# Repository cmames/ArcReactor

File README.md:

# ⚛️ Arc Reactor Mark II - Open Source Prop Replica

## Project Overview
This project provides all necessary files (Electronics, 3D Models, and Firmware) to build a sophisticated, functional replica of the Mark II Arc Reactor with an emphasis on realistic plasma motion effects.

The design focuses on a premium, compact, and fully wireless solution for a dynamic display prop. The core feature is the smooth, chaotic rotation effect of the ice-blue plasma filaments, controlled by custom firmware.

## Key Features
* **Ice-Blue Plasma Effect:** Uses 5 custom LED filaments (300mm length) controlled via PWM for dynamic, realistic light effects (rotation, chaos, flickering).
* **Standalone Power:** Features an integrated Li-Po battery (150-200mAh) and a full power management system (TP4056 for charging, Mini Boost to 5V).
* **Amovibility & Latency:** Designed to be easily detached from its magnetic display stand, maintaining the light effect for a short duration thanks to the embedded power system.
* **Microcontroller:** ESP32-C3 Mini for high-speed PWM control (5 dedicated LEDC channels) and battery monitoring (ADC).
* **SMD Component Integration:** Custom circular PCB design utilizing SOT-23 MOSFETs for minimal footprint and optimal soldering simplicity.
* **Optics:** Use of a 3D-printed transparent PETG for superior light diffusion and visual quality.

## Project Files Included
This repository is organized into the following directories:

| Directory | Content | Description |
| :--- | :--- | :--- |
| **`Firmware/`** | Arduino/PlatformIO Code | Source code (C/C++) for the ESP32-C3, including PWM routines, ADC battery monitoring, and the 'flicker/fade-out' logic. |
| **`Electronics/`** | KiCad Project Files | Schematics, PCB layout files (circular design), and custom component libraries (e.g., SOT-23 footprints, ESP32-C3 module). |
| **`Mechanical/`** | STL / FreeCAD Files | 3D models for the reactor casing, the flexible TPU casting mold, and the magnetic display stand components. |
| **`Documentation/`** | Datasheets & Guides | Bill of Materials (BOM), wiring diagrams, and assembly guides. |

## License
This project is released under the **GNU General Public License v3.0 (GPL-3.0)**. See the `LICENSE` file for more details.

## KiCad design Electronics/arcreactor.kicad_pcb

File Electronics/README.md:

# ⚛️ Arc Reactor Mark II - Open Source Prop Replica

| Directory | Content | Description |
| :--- | :--- | :--- |
| **`Electronics/`** | KiCad Project Files | Schematics, PCB layout files (circular design), and custom component libraries (e.g., SOT-23 footprints, ESP32-C3 module). |

## License
This project is released under the **GNU General Public License v3.0 (GPL-3.0)**. See the `LICENSE` file for more details.

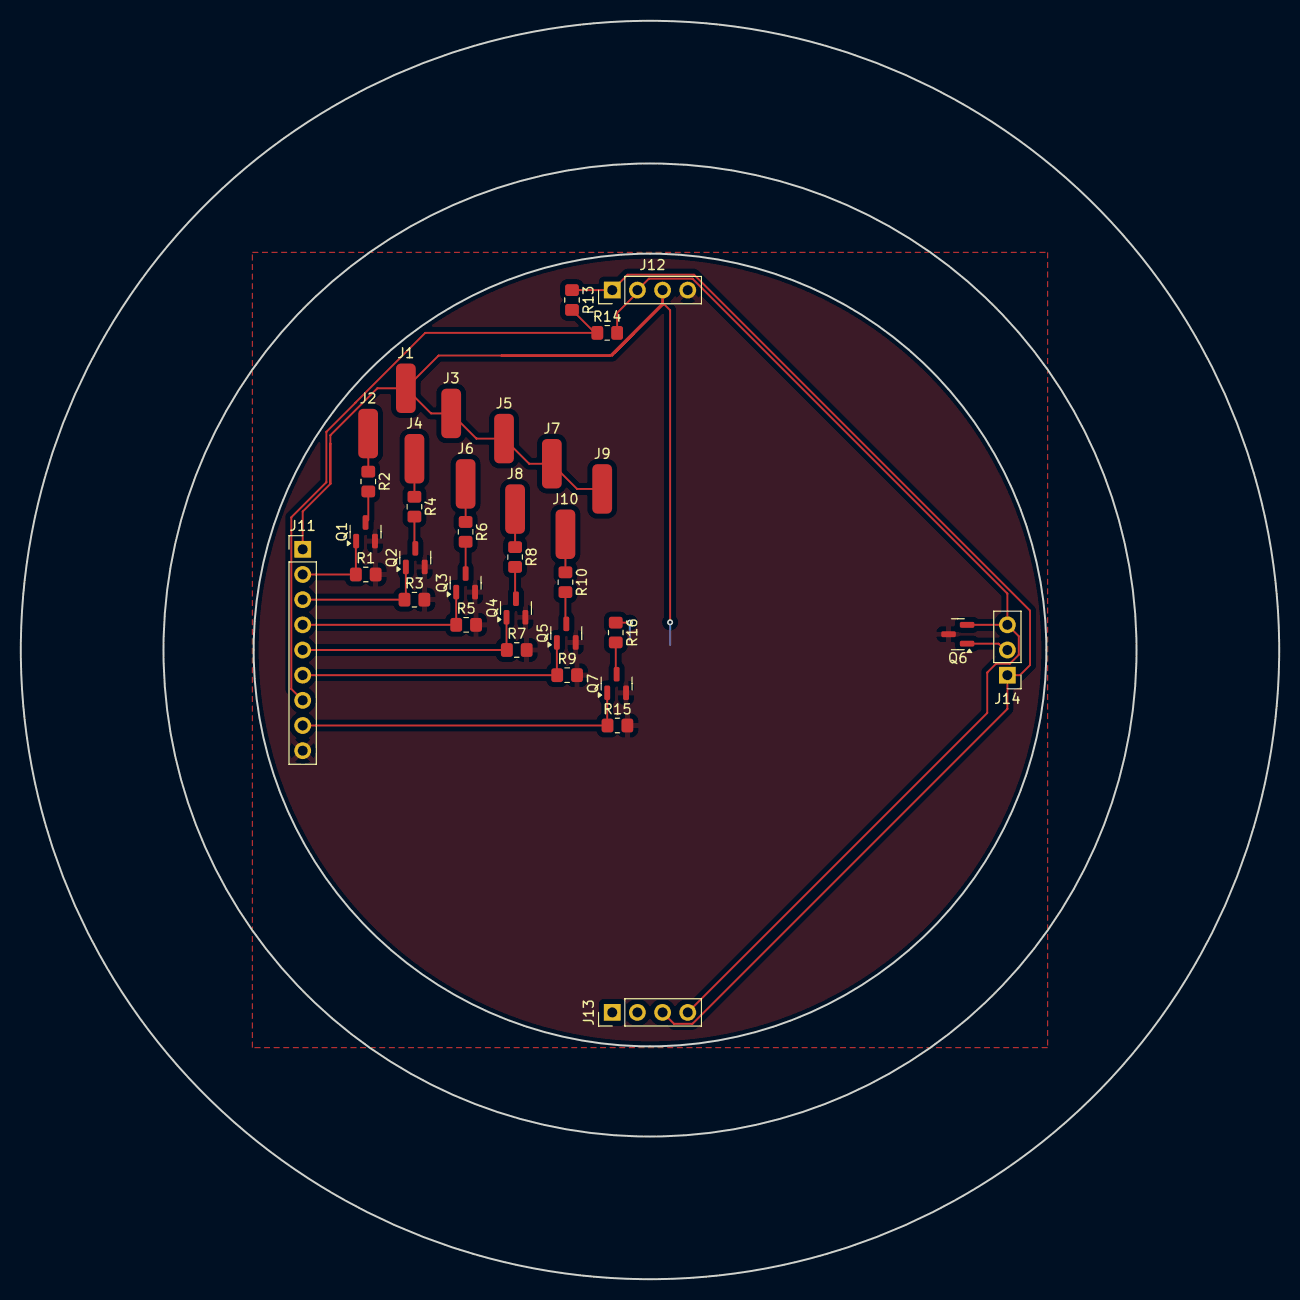
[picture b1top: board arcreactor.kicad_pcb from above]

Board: 2 copper layers, 127.0 x 127.0 mm, 36 parts (1 on the bottom side), 24 nets.

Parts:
D0: LED; LED_PLCC_2835_Handsoldering
J1, J2, J3, J4, J5, J6, J7, J8, J9, J10: Conn_01x01_Socket; SolderWirePad_1x01_SMD_2x5mm
J11: ESP C3 mini; PinHeader_1x09_P2.54mm_Vertical
J12: Boost; PinHeader_1x04_P2.54mm_Vertical
J13: TP4056; PinHeader_1x04_P2.54mm_Vertical
J14: touch; PinHeader_1x03_P2.54mm_Vertical
Q1, Q2, Q3, Q4, Q5, Q6, Q7: Q_NMOS_GSD; SOT-23
R1, R3, R5, R7, R9, R14, R15: 10k; R_0805_2012Metric_Pad1.20x1.40mm_HandSolder
R2, R4, R6, R8, R10: 47; R_0805_2012Metric_Pad1.20x1.40mm_HandSolder
R13: 33k; R_0805_2012Metric_Pad1.20x1.40mm_HandSolder
R16: R; R_0805_2012Metric_Pad1.20x1.40mm_HandSolder

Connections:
LED0: J11.8, Q7.1 (G), R15.1
LED1: J11.2, Q1.1 (G), R1.1
LED2: J11.3, Q2.1 (G), R3.1
LED3: J11.4, Q3.1 (G), R5.1
LED4: J11.5, Q4.1 (G), R7.1
LED5: J11.6, Q5.1 (G), R9.1
LiPo +: J12.1, J13.3, J14.1, R13.1
LiPo -: J12.2, J13.4, J14.3, Q6.2 (S), R14.2
unnamed: D0.1 (K), R16.1
unnamed: J2.1, R2.1
unnamed: J4.1, R4.1
unnamed: J6.1, R6.1
unnamed: J8.1, R8.1
unnamed: J10.1, R10.1
unnamed: J11.7, R13.2, R14.1
unnamed: J14.2, Q6.1 (G)
unnamed: Q1.3 (D), R2.2
unnamed: Q2.3 (D), R4.2
unnamed: Q3.3 (D), R6.2
unnamed: Q4.3 (D), R8.2
unnamed: Q5.3 (D), R10.2
unnamed: Q7.3 (D), R16.2
boost out +5V: D0.2 (A), J1.1, J3.1, J5.1, J7.1, J9.1, J11.1, J12.3
boost out GND: J11.9, J12.4, Q1.2 (S), Q2.2 (S), Q3.2 (S), Q4.2 (S), Q5.2 (S), Q6.3 (D), Q7.2 (S), R1.2, R3.2, R5.2, R7.2, R9.2, R15.2

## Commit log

2025-12-13 electronic
2025-12-13 reorg
2026-02-20 feat : start dev
2026-02-20 feat : first lines
